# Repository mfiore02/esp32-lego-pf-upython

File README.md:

# ESP32 Lego Power Functions Controller

MicroPython implementation of a wireless Lego Power Functions motor controller system using ESP32-C3 and ESP-NOW.

## Overview

This project implements a low-latency wireless control system for Lego Power Functions motors, consisting of:

- **Handheld Controller**: Potentiometer for speed, button for direction toggle, 2xAA powered
- **Train Receiver**: Dual TB6612 motor driver, 2S LiPo with USB-C charging, fits in 8x4 stud Lego box
- **Communication**: ESP-NOW protocol for <10ms latency
- **Pairing**: Button-based pairing with MAC addresses stored in NVS flash

## System Architecture

```
┌─────────────────────┐                    ┌─────────────────────┐
│  CONTROLLER         │                    │  TRAIN RECEIVER     │
│  (Handheld)         │   ESP-NOW (WiFi)   │  (On Train)         │
├─────────────────────┤◄──────────────────►├─────────────────────┤
│ • Potentiometer     │   20Hz updates     │ • TB6612 Driver     │
│ • Direction Button  │   Low latency      │ • 2x Motors         │
│ • Status LED        │   Paired MAC       │ • Pair Button       │
│ • 2xAA Power        │   filtering        │ • 2S LiPo + BMS     │
└─────────────────────┘                    └─────────────────────┘
```

## Project Structure

```
esp32-lego-pf-upython/
├── lib/                          # Shared modules (both devices)
│   ├── espnow_protocol.py        # ESP-NOW wrapper + message protocol
│   ├── config_manager.py         # NVM storage abstraction (versioned)
│   ├── button.py                 # Debounced button driver
│   ├── led.py                    # LED patterns (solid, blink, etc)
│   ├── motor_driver.py           # TB6612 abstraction
│   ├── potentiometer.py          # ADC with dead zone handling
│   ├── battery.py                # 2S LiPo voltage monitoring (receiver)
│   └── hardware.py               # GPIO pin assignments (both devices)
│
├── controller/
│   ├── boot.py                   # Minimal - sets up path
│   └── main.py                   # Controller app entry point
│
├── receiver/
│   ├── boot.py                   # Minimal - sets up path
│   └── main.py                   # Receiver app entry point
│
├── tests/                        # Unit tests (run on host)
│   ├── test_espnow_protocol.py
│   ├── test_config_manager.py
│   └── test_potentiometer.py
│
├── hwil/                         # Hardware-in-loop test scripts
│   ├── test_button.py            # Flash to device, test button
│   ├── test_motors.py
│   └── test_espnow_ping.py
│
├── tools/
│   ├── flash_controller.sh       # Deploy to controller
│   ├── flash_receiver.sh         # Deploy to receiver
│   └── cli.py                    # USB-C serial config tool
│
├── docs/
│   └── lego_pf_controller_build_guide.pdf
│
└── README.md
```

## Hardware Requirements

### Train Receiver (Per-unit cost: $26-36)
- ESP32-C3 SuperMini
- TB6612FNG dual H-bridge motor driver
- USB-C 2S BMS (balanced charging)
- 2S LiPo 350mAh (45×15×14mm with balance lead)
- AMS1117-3.3V voltage regulator
- Mini slide switch (SPST, 3A+)
- Momentary pushbutton (or use onboard BOOT button)
- 2x Lego PF extension cables
- Prototype board and wiring

### Handheld Controller (Per-unit cost: $8-15)
- ESP32-C3 SuperMini
- 10K potentiometer (linear, panel mount)
- Knob for potentiometer
- Momentary pushbutton (direction + pairing)
- 2xAA battery holder
- SPST slide switch
- LED + 1K resistor
- Small project enclosure

See `docs/lego_pf_controller_build_guide.pdf` for detailed wiring diagrams and assembly instructions.

## GPIO Assignments

### Controller
| Function | GPIO | Notes |
|----------|------|-------|
| Potentiometer (ADC) | GPIO1 | Speed control |
| Status LED | GPIO8 | Status indicator |
| Direction Button | GPIO10 | Toggle direction + pairing mode |

### Receiver
| Function | GPIO | Notes |
|----------|------|-------|
| Motor 1 PWM | GPIO2 | TB6612 PWMA |
| Motor 1 IN1 | GPIO4 | TB6612 AIN1 |
| Motor 1 IN2 | GPIO3 | TB6612 AIN2 |
| Motor 2 PWM | GPIO5 | TB6612 PWMB |
| Motor 2 IN1 | GPIO7 | TB6612 BIN1 |
| Motor 2 IN2 | GPIO6 | TB6612 BIN2 |
| Status LED | GPIO8 | Status indicator |
| Pairing Button | GPIO10 | External button (active low) |
| Battery B+ (ADC) | GPIO0 | Full battery voltage via 100k/39k divider |
| Battery BM (ADC) | GPIO1 | Mid-point voltage via 33k/47k divider |

## Configuration Format

Configuration is stored in JSON format with versioning:

```json
{
  "version": 1,
  "device_type": "controller",
  "paired": true,
  "train_mac": [0x12, 0x34, 0x56, 0x78, 0x9A, 0xBC],
  "pot_calibration": {
    "min": 100,
    "max": 3995,
    "zero_band": 50
  }
}
```

## Development Workflow

This project follows an **incremental, test-driven development** approach:

1. Develop a module with clear interface
2. Write unit tests (where applicable)
3. Create HWIL test script
4. Validate on actual hardware
5. Move to next module

### Development Phases

#### Phase 1: Foundation Modules
1. ✅ `lib/config_manager.py` - NVM storage with versioning
2. ✅ `lib/button.py` - Debounced button input
3. ✅ `lib/led.py` - LED pattern control
4. ✅ `lib/potentiometer.py` - ADC with dead zone calibration
5. ✅ `lib/motor_driver.py` - TB6612 PWM control (hardware validated)

#### Phase 2: Communication Layer
6. ✅ `lib/espnow_protocol.py` - Message protocol and ESP-NOW wrapper (hardware validated)

#### Phase 3: Application Logic
7. ✅ `controller/main.py` - Controller application with pairing and control loop
8. ✅ `receiver/main.py` - Receiver application with motor control and safety timeout
9. ✅ End-to-end hardware validation and pairing flow testing (**SYSTEM WORKING!**)

#### Phase 4: Configuration & Deployment
10. ✅ Deployment scripts (controller, receiver, HWIL)
11. ⬜ `tools/cli.py` - USB-C serial configuration tool (optional)
12. ⬜ Final documentation and build guide updates

#### Phase 5: PCB Design
13. ✅ Controller schematic (P-FET power switching, GPIO assignments)
14. ✅ Receiver schematic (P-FET switching, TB6612 H-bridge, buck converter, BMS)
15. ✅ Custom symbol library (ESP32-C3-SuperMini, TB6612FNG, MP1584EN, 2S BMS)
16. ✅ Custom footprints (ESP32 module, slide switch, push button)
17. ⬜ Add decoupling capacitors to both schematics
18. ⬜ Custom footprints for breakout boards (2S BMS, MP1584EN buck, TB6612FNG)
19. ⬜ Controller PCB layout
20. ⬜ Receiver PCB layout

## Installation & Deployment

### Prerequisites
```bash
pip install esptool mpremote
```

### Flashing MicroPython Firmware
```bash
# Download ESP32-C3 firmware from micropython.org
# Erase flash
esptool.py --chip esp32c3 erase_flash

# Flash MicroPython
esptool.py --chip esp32c3 write_flash -z 0x0 ESP32_GENERIC_C3-*.bin
```

### Deploying Application Code

**Controller:**
```bash
./tools/flash_controller.sh /dev/ttyUSB0
```

**Receiver:**
```bash
./tools/flash_receiver.sh /dev/ttyUSB0
```

## Usage

### Pairing Procedure
1. Hold pairing button on train while powering on → motors twitch once
2. Hold direction button on controller while powering on → LED blinks rapidly
3. Wait 1-3 seconds → devices pair automatically
4. Train motors twitch twice, controller LED goes solid
5. Both devices reboot into normal mode

### Normal Operation
- **Speed**: Turn potentiometer (CCW=stop, CW=max)
- **Direction**: Press button to toggle forward/reverse
- **LED**: On=forward, Off=reverse
- **Safety**: Motors stop if no signal for 500ms

### Configuration via CLI
```bash
python tools/cli.py /dev/ttyUSB0

>>> config.show()
Paired: True
Train MAC: 12:34:56:78:9A:BC

>>> config.unpair()
Unpaired successfully
```

## Testing

### Unit Tests (Host)
```bash
python -m pytest tests/
```

### Hardware-in-Loop Tests
```bash
# Flash HWIL test to device (Windows example with COM port)
mpremote connect COM3 fs cp hwil/test_button.py :main.py

# Linux/Mac example
mpremote connect /dev/ttyUSB0 fs cp hwil/test_button.py :main.py

# Monitor serial output with mpremote
mpremote connect COM3 repl

# Or use screen on Linux/Mac
screen /dev/ttyUSB0 115200
```

## Safety Features

- 500ms communication timeout stops motors if signal lost
- BMS protection: overcharge, over-discharge, short-circuit
- Paired MAC filtering prevents unauthorized control
- Motor safety stop on receiver boot

## Future Enhancements

- [x] Battery level monitoring (`lib/battery.py` — voltage, per-cell, status, percentage)
- [ ] Battery telemetry (receiver → controller over ESP-NOW)
- [ ] Multiple train support (train selector on controller)
- [ ] Speed limit profiles (parental controls)
- [ ] Additional GPIO features (lights, sound effects)
- [ ] Remote configuration over ESP-NOW
- [ ] Web-based configuration interface

## License

See [LICENSE](LICENSE) file for details.

## References

- Build guide: `docs/lego_pf_controller_build_guide.pdf`
- ESP-NOW documentation: https://docs.espressif.com/projects/esp-idf/en/latest/esp32c3/api-reference/network/esp_now.html
- MicroPython ESP32: https://docs.micropython.org/en/latest/esp32/quickref.html

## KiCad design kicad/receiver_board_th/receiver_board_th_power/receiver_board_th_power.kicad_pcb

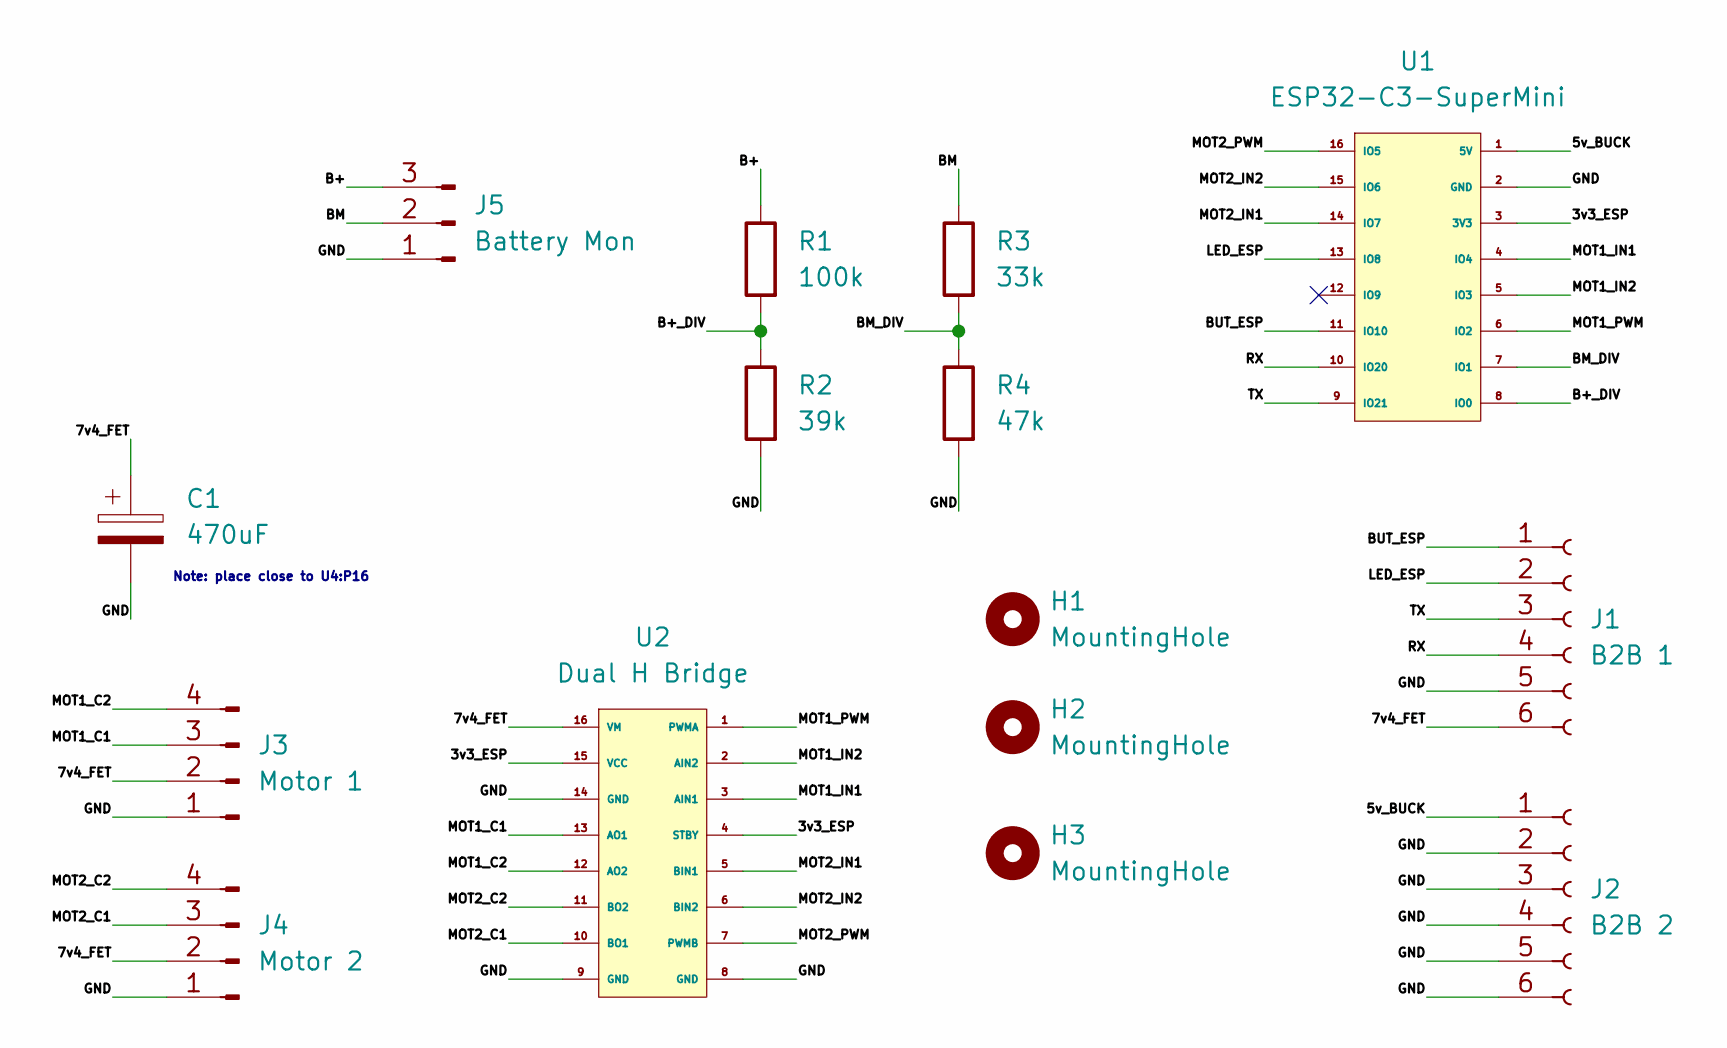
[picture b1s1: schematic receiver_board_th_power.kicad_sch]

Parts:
C1: 470uF; CP_Radial_D8.0mm_P5.00mm
H1, H2, H3: MountingHole; MountingHole_2.2mm_M2_Pad_TopBottom
J1: B2B 1; PinSocket_1x06_P2.54mm_Vertical
J2: B2B 2; PinSocket_1x06_P2.54mm_Vertical
J3: Motor 1; JST_XH_B4B-XH-A_1x04_P2.50mm_Vertical
J4: Motor 2; JST_XH_B4B-XH-A_1x04_P2.50mm_Vertical
J5: Battery Mon; PinHeader_1x03_P2.54mm_Vertical
R1: 100k; R_Axial_DIN0207_L6.3mm_D2.5mm_P7.62mm_Horizontal
R2: 39k; R_Axial_DIN0207_L6.3mm_D2.5mm_P7.62mm_Horizontal
R3: 33k; R_Axial_DIN0207_L6.3mm_D2.5mm_P7.62mm_Horizontal
R4: 47k; R_Axial_DIN0207_L6.3mm_D2.5mm_P7.62mm_Horizontal
U1: ESP32-C3-SuperMini
U2: Dual H Bridge; TB6612FNG

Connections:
/3v3_ESP: U1.3 (3V3), U2.4 (STBY), U2.15 (VCC)
/5v_BUCK: J2.1, U1.1 (5V)
/7v4_FET: C1.1, J1.6, J3.2, J4.2, U2.16 (VM)
/B+: J5.3, R1.1
/B+_DIV: R1.2, R2.1, U1.8 (IO0)
/BM: J5.2, R3.1
/BM_DIV: R3.2, R4.1, U1.7 (IO1)
/BUT_ESP: J1.1, U1.11 (IO10)
/GND: C1.2, J1.5, J2.2, J2.3, J2.4, J2.5, J2.6, J3.1, J4.1, J5.1, R2.2, R4.2, U1.2 (GND), U2.8 (GND), U2.9 (GND), U2.14 (GND)
/LED_ESP: J1.2, U1.13 (IO8)
/MOT1_C1: J3.3, U2.13 (AO1)
/MOT1_C2: J3.4, U2.12 (AO2)
/MOT1_IN1: U1.4 (IO4), U2.3 (AIN1)
/MOT1_IN2: U1.5 (IO3), U2.2 (AIN2)
/MOT1_PWM: U1.6 (IO2), U2.1 (PWMA)
/MOT2_C1: J4.3, U2.10 (BO1)
/MOT2_C2: J4.4, U2.11 (BO2)
/MOT2_IN1: U1.14 (IO7), U2.5 (BIN1)
/MOT2_IN2: U1.15 (IO6), U2.6 (BIN2)
/MOT2_PWM: U1.16 (IO5), U2.7 (PWMB)
/RX: J1.4, U1.10 (IO20)
/TX: J1.3, U1.9 (IO21)

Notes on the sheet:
Note: place close to U4:P16

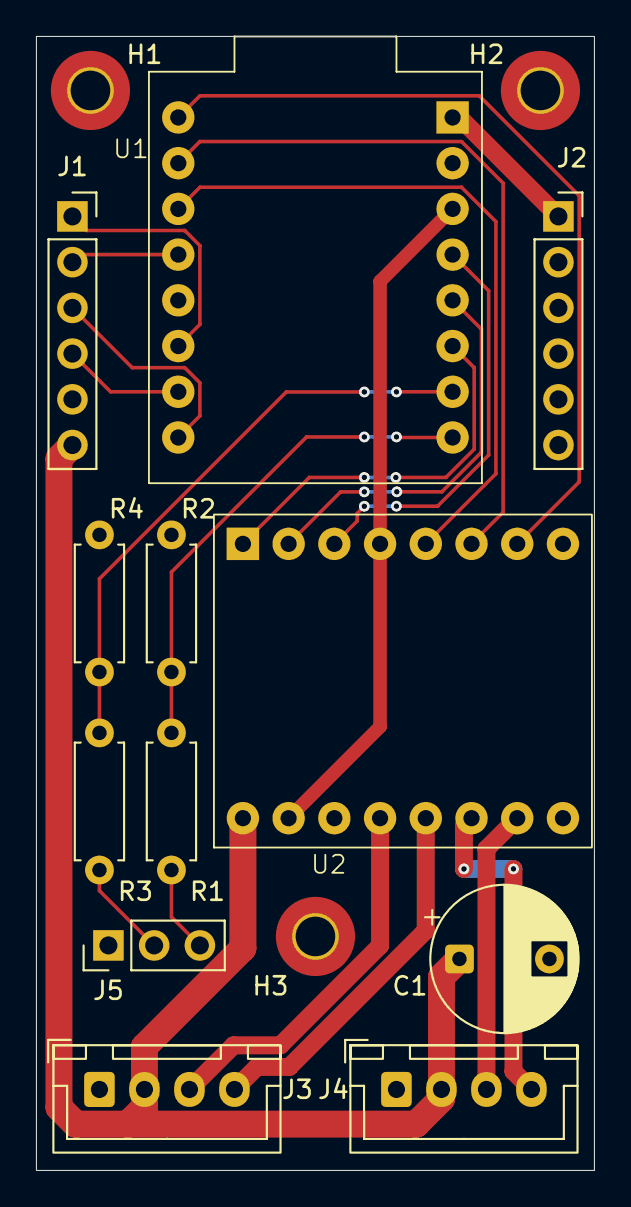
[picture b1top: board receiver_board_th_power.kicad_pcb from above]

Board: 2 copper layers, 31.0 x 63.0 mm, 15 parts (0 on the bottom side), 22 nets.

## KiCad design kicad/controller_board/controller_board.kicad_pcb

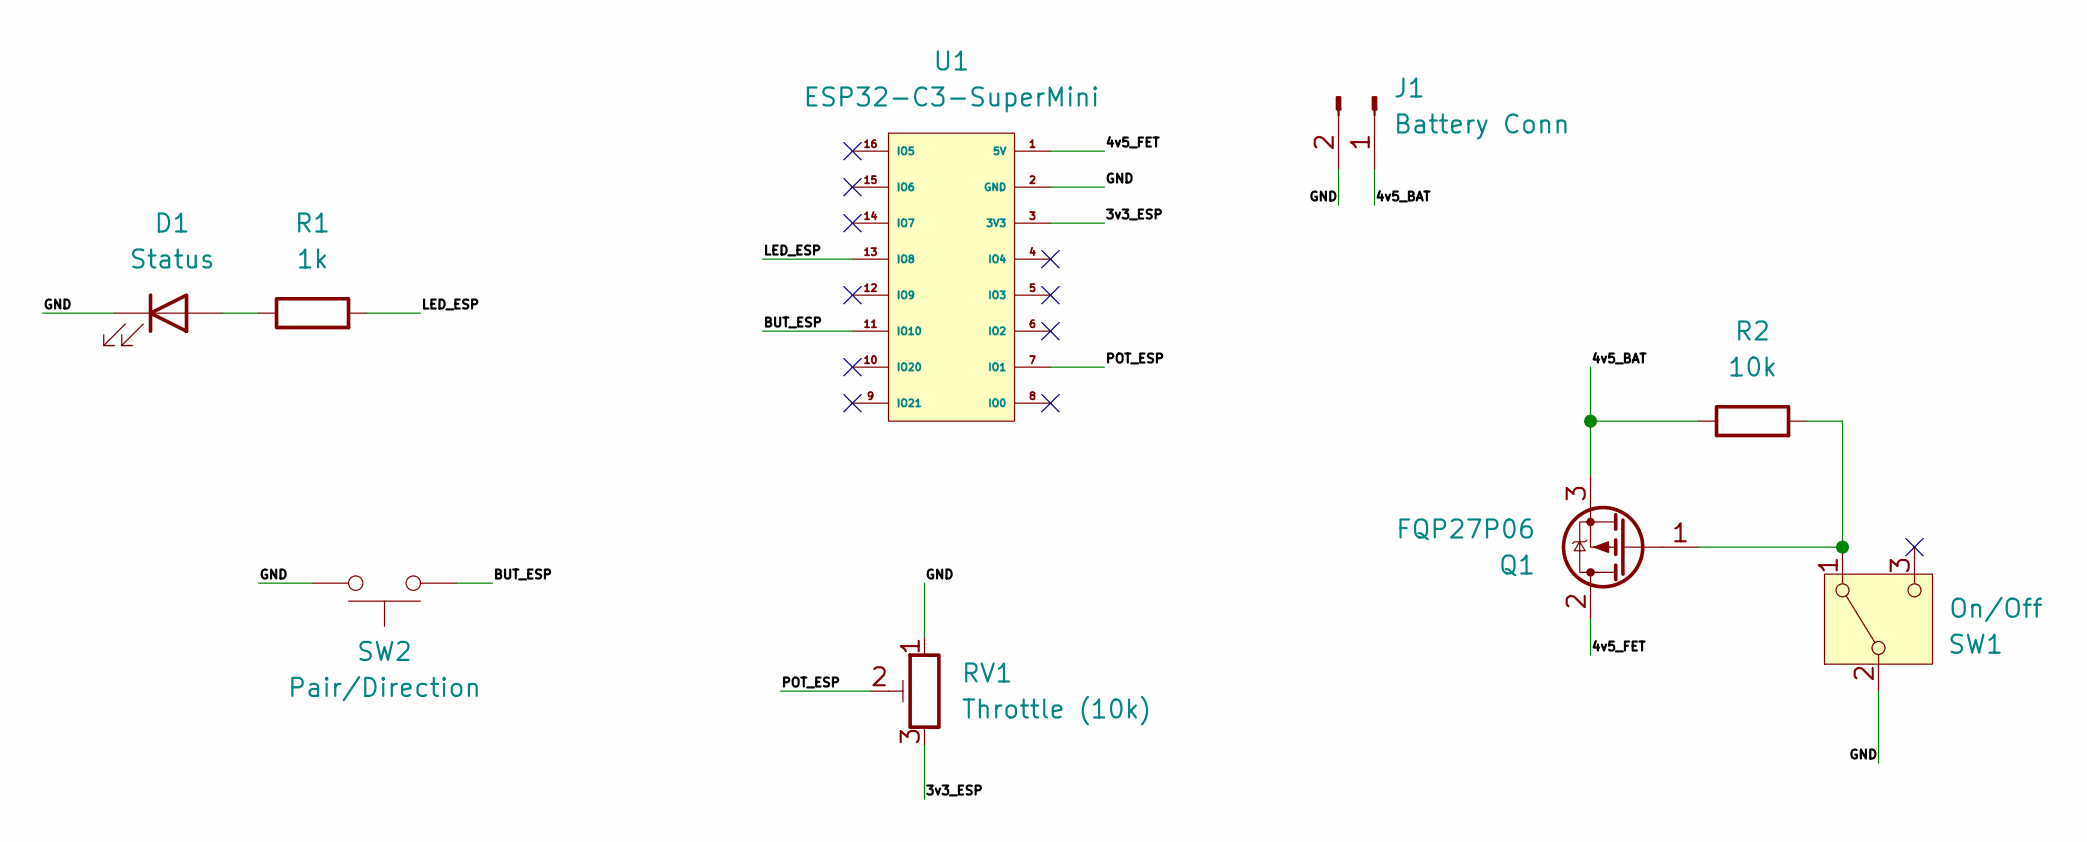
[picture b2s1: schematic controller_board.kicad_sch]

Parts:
D1: Status; LED_D5.0mm
J1: Battery Conn; PinHeader_1x02_P2.54mm_Horizontal
Q1: FQP27P06; TO-220-3_Vertical
R1: 1k; R_Axial_DIN0207_L6.3mm_D2.5mm_P7.62mm_Horizontal
R2: 10k; R_Axial_DIN0207_L6.3mm_D2.5mm_P7.62mm_Horizontal
RV1: Throttle (10k); Potentiometer_Alps_RK163_Single_Horizontal
SW1: On/Off; Slide_Switch_SPDT_12D00G
SW2: Pair/Direction
U1: ESP32-C3-SuperMini

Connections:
/3v3_ESP: RV1.3, U1.3 (3V3)
/4v5_BAT: J1.1, Q1.3 (S), R2.1
/4v5_FET: Q1.2 (D), U1.1 (5V); also elsewhere on the board
/BUT_ESP: SW2.2, U1.11 (IO10)
/GND: D1.1 (K), J1.2, RV1.1, SW1.2 (B), SW2.1, U1.2 (GND); also elsewhere on the board
/LED_ESP: R1.2, U1.13 (IO8)
/POT_ESP: RV1.2, U1.7 (IO1)
unnamed: D1.2 (A), R1.1
unnamed: Q1.1 (G), R2.2, SW1.1 (A)

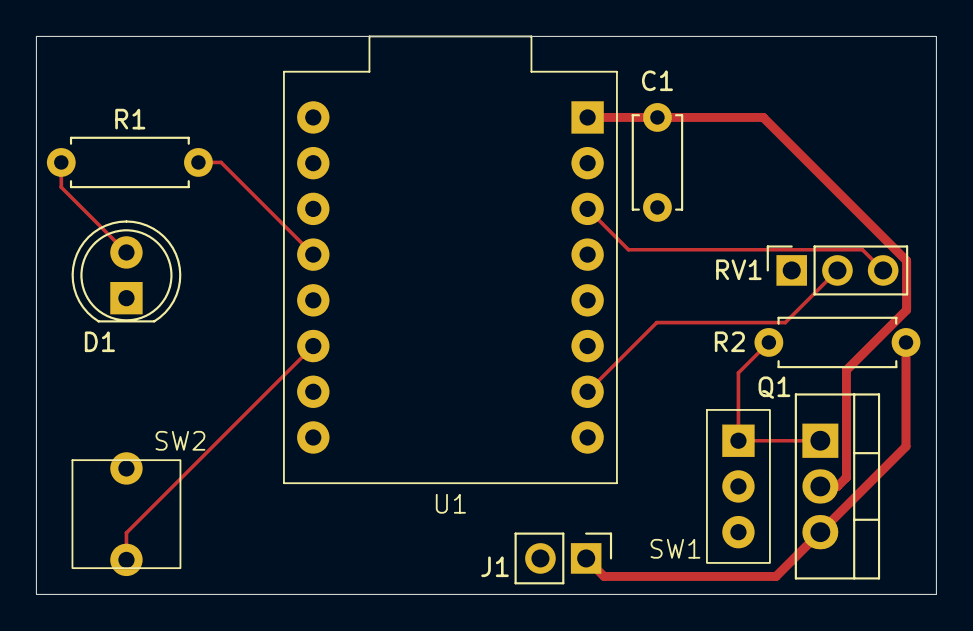
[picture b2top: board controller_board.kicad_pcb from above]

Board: 2 copper layers, 50.0 x 31.0 mm, 10 parts (0 on the bottom side), 9 nets.

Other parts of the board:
C1: 0.1uF; C_Disc_D5.0mm_W2.5mm_P5.00mm

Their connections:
/4v5_FET: C1.1; also elsewhere on the board
/GND: C1.2; also elsewhere on the board

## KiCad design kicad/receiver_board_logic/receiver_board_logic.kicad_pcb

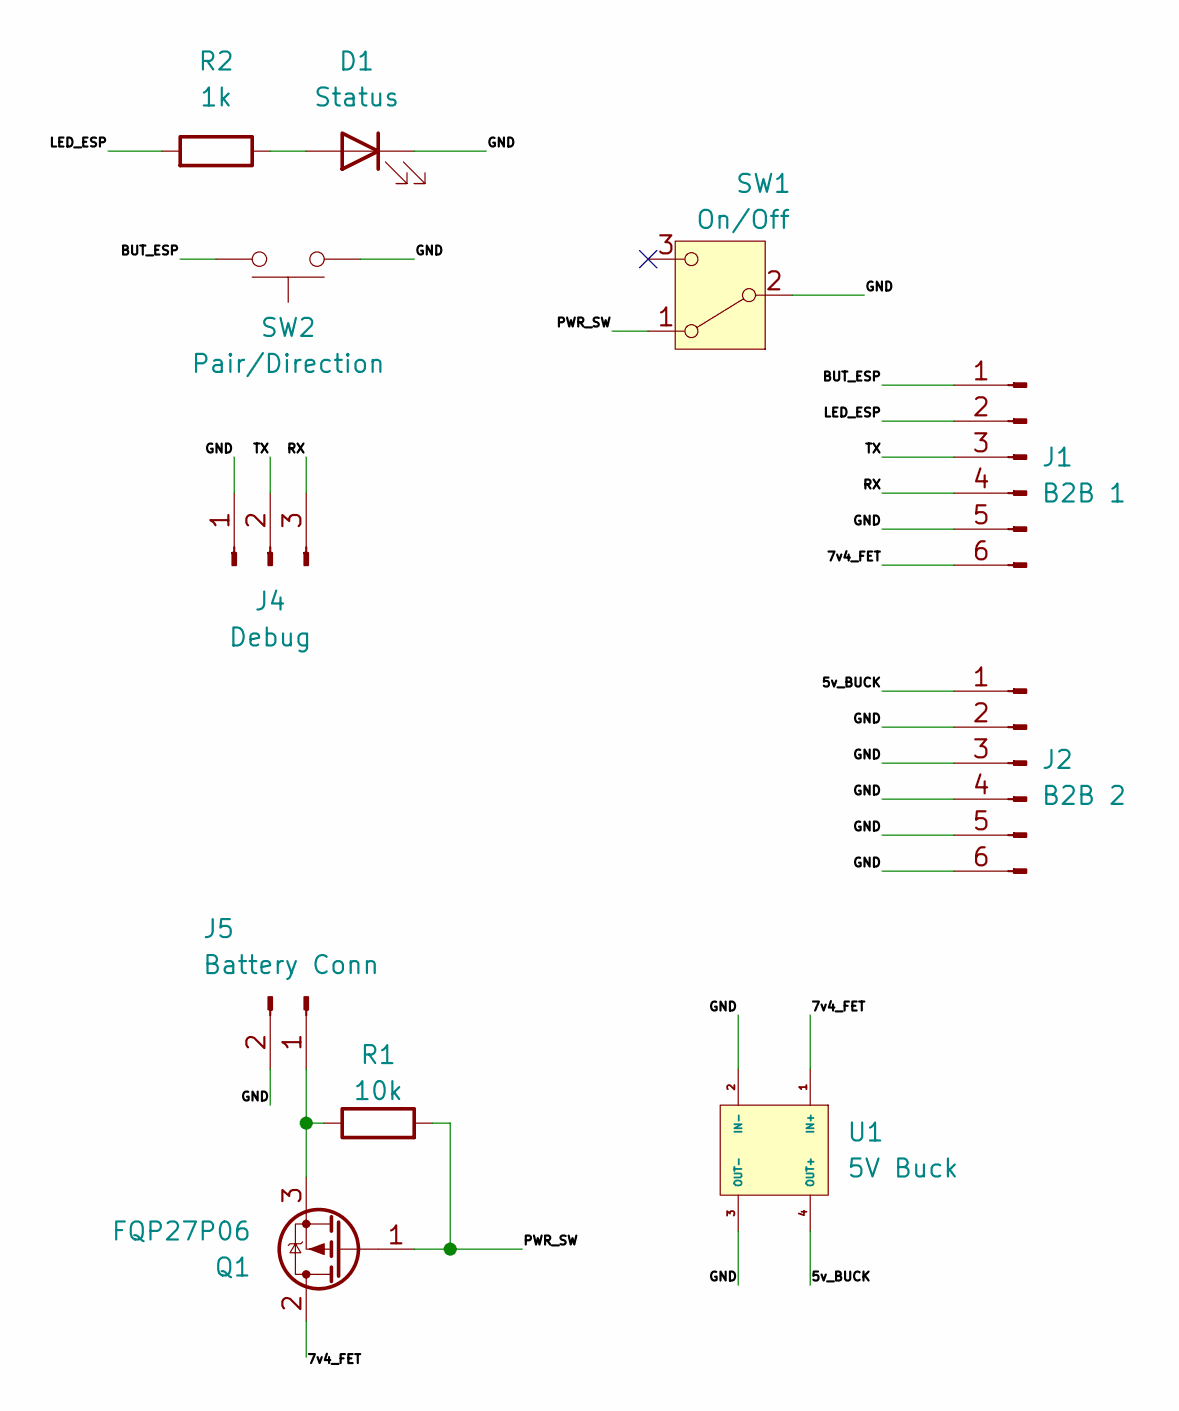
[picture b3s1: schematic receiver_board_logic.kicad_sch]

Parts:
D1: Status; LED_D5.0mm
J1: B2B 1; PinHeader_1x06_P2.54mm_Vertical
J2: B2B 2; PinHeader_1x06_P2.54mm_Vertical
J4: Debug; PinHeader_1x03_P2.54mm_Vertical
J5: Battery Conn; PinHeader_1x02_P2.54mm_Vertical
Q1: FQP27P06; TO-220-3_Vertical
R1: 10k; R_Axial_DIN0207_L6.3mm_D2.5mm_P7.62mm_Horizontal
R2: 1k; R_Axial_DIN0207_L6.3mm_D2.5mm_P7.62mm_Horizontal
SW1: On/Off; Slide_Switch_SPDT_12D00G
SW2: Pair/Direction; Push_Button_TSD016
U1: 5V Buck; MP1584EN

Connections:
/5v_BUCK: J2.1, U1.4 (OUT+)
/7v4_FET: J1.6, Q1.2 (D), U1.1 (IN+)
/BUT_ESP: J1.1, SW2.2
/GND: D1.1 (K), J1.5, J2.2, J2.3, J2.4, J2.5, J2.6, J4.1, J5.2, SW1.2 (B), SW2.1, U1.2 (IN-), U1.3 (OUT-)
/LED_ESP: J1.2, R2.2
/PWR_SW: Q1.1 (G), R1.2, SW1.1 (A)
/RX: J1.4, J4.3
/TX: J1.3, J4.2
unnamed: D1.2 (A), R2.1
unnamed: J5.1, Q1.3 (S), R1.1

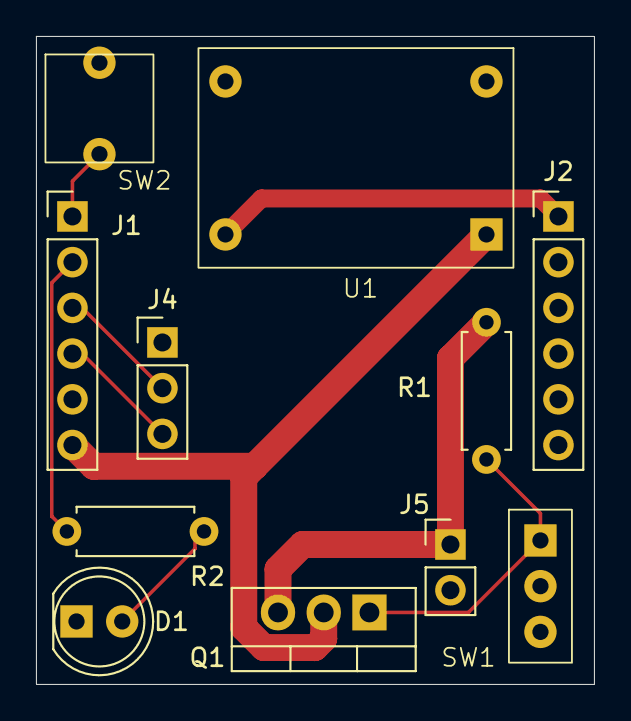
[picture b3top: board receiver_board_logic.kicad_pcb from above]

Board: 2 copper layers, 31.0 x 36.0 mm, 11 parts (0 on the bottom side), 10 nets.

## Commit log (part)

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2025-12-29 Add comprehensive README and project architecture
    - Document system architecture and component overview
    - Define modular project structure (dual-app with shared lib/)
    - Outline incremental development workflow (TDD + HWIL)
    - Add hardware requirements and GPIO assignments
    - Include configuration format with versioning
    - Document deployment and testing procedures
2025-12-29 Add project directory structure with documentation
    - Create lib/, controller/, receiver/, tests/, hwil/, tools/ directories
    - Add README.md in each directory explaining purpose and usage
    - Establish foundation for incremental module development
2026-01-10 Additional updates after testing: * add 3s delay in main apps before starting to allow time for repl connection * consolidate disparate pairing flows in receiver * print pwm for both motors in receiv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
2026-01-11 Remove audit report files as those issues have been resolved
2026-01-23 Finished generating footprints for all parts. Receiver boards layout and stacking order is still TBD, so renamed them from "uppper" and "lower" to "power" and "logic" as that will likely be the rough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
2026-01-25 Elininate dead space on right side of controller PCB
2026-01-31 Investigating a SMD version of receiver board, so renaming existing projects with _th and reorganizing
2026-01-31 Add M2 mounting holes to receiver power board
